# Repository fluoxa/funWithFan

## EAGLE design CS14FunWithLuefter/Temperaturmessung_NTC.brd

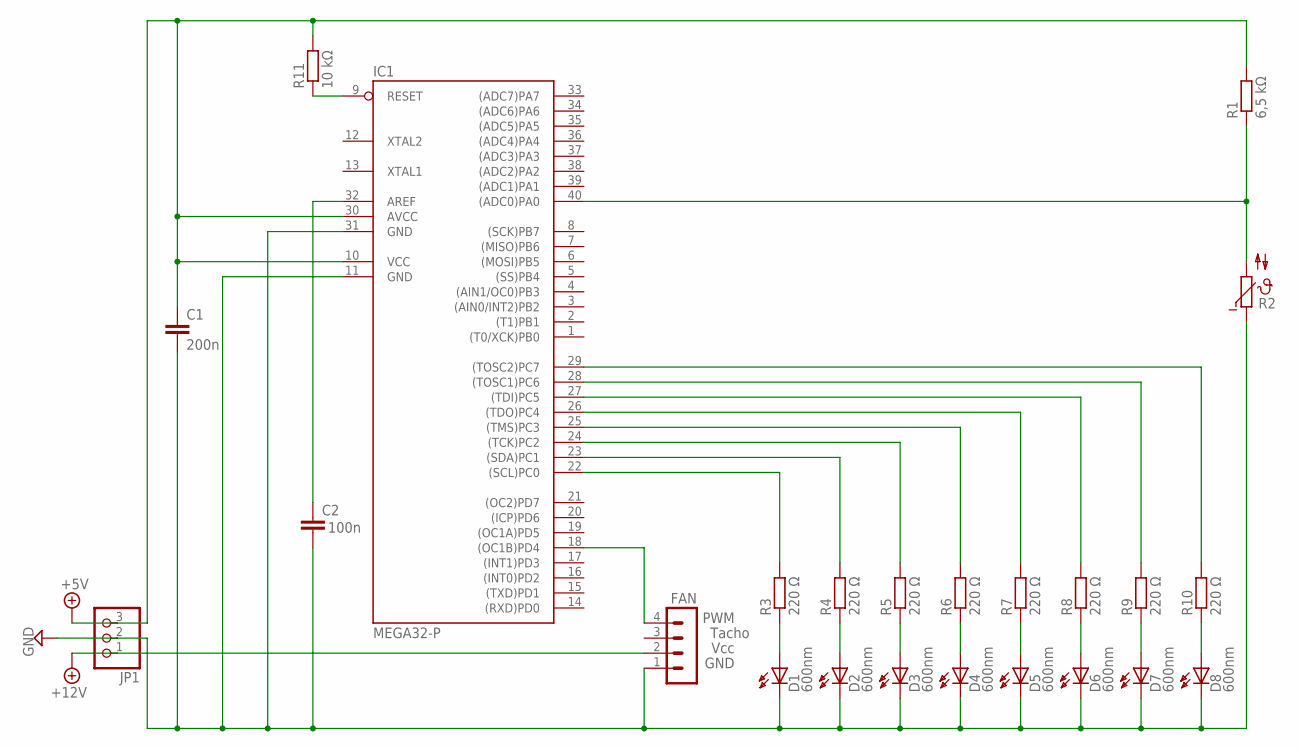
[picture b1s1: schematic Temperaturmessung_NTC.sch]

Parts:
C1: 200n; C2.5-2
C2: C2.5/2; C2.5-2
D1, D2, D3, D4, D5, D6, D7, D8: 600nm; HLMP6
FAN: MA04-1; MPN Tacho
IC1: MEGA32-P; DIL40
JP1: PINHD-1X3/90; 1X03/90
R1: 6,5 kΩ; 0309/12
R2: NTC644A; N644A
R3, R4, R5, R6, R7, R8, R9, R10: 220 Ω; 0309/12
R11: 10 kΩ; 0309/12

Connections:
+5V: C1.1, IC1.10 (VCC), IC1.30 (AVCC), JP1.3, R1.2, R11.2
+12V: FAN.2, JP1.1
GND: C1.2, C2.2, D1.K, D2.K, D3.K, D4.K, D5.K, D6.K, D7.K, D8.K, FAN.1, IC1.11 (GND), IC1.31 (GND), JP1.2, R2.1
unnamed: IC1.22 ((SCL)PC0), R3.2
unnamed: IC1.40 ((ADC0)PA0), R1.1, R2.2
unnamed: FAN.4, IC1.18 ((OC1B)PD4)
unnamed: IC1.23 ((SDA)PC1), R4.2
unnamed: C2.1, IC1.32 (AREF)
unnamed: IC1.24 ((TCK)PC2), R5.2
unnamed: IC1.25 ((TMS)PC3), R6.2
unnamed: IC1.26 ((TDO)PC4), R7.2
unnamed: IC1.27 ((TDI)PC5), R8.2
unnamed: IC1.28 ((TOSC1)PC6), R9.2
unnamed: IC1.29 ((TOSC2)PC7), R10.2
unnamed: D1.A, R3.1
unnamed: D2.A, R4.1
unnamed: D3.A, R5.1
unnamed: D4.A, R6.1
unnamed: D5.A, R7.1
unnamed: D6.A, R8.1
unnamed: D7.A, R9.1
unnamed: D8.A, R10.1
unnamed: IC1.9 (RESET), R11.1

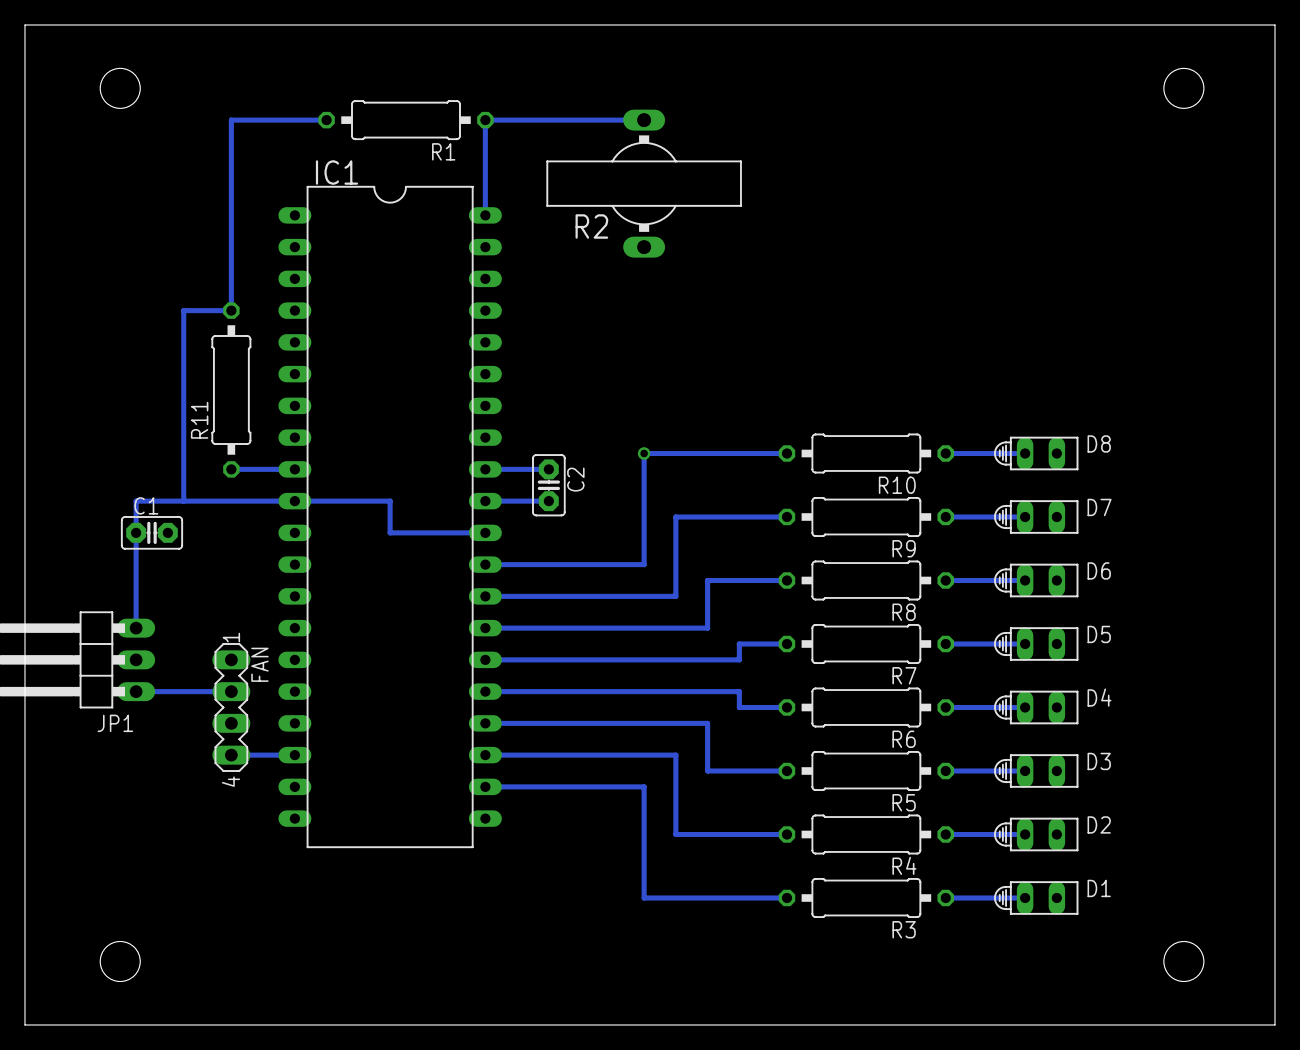
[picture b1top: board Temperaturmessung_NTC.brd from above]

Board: 2 copper layers, 100.0 x 80.0 mm, 24 parts (0 on the bottom side), 23 nets.

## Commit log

2017-05-18 initiale Kacke
2017-05-20 vortrag mein teil
